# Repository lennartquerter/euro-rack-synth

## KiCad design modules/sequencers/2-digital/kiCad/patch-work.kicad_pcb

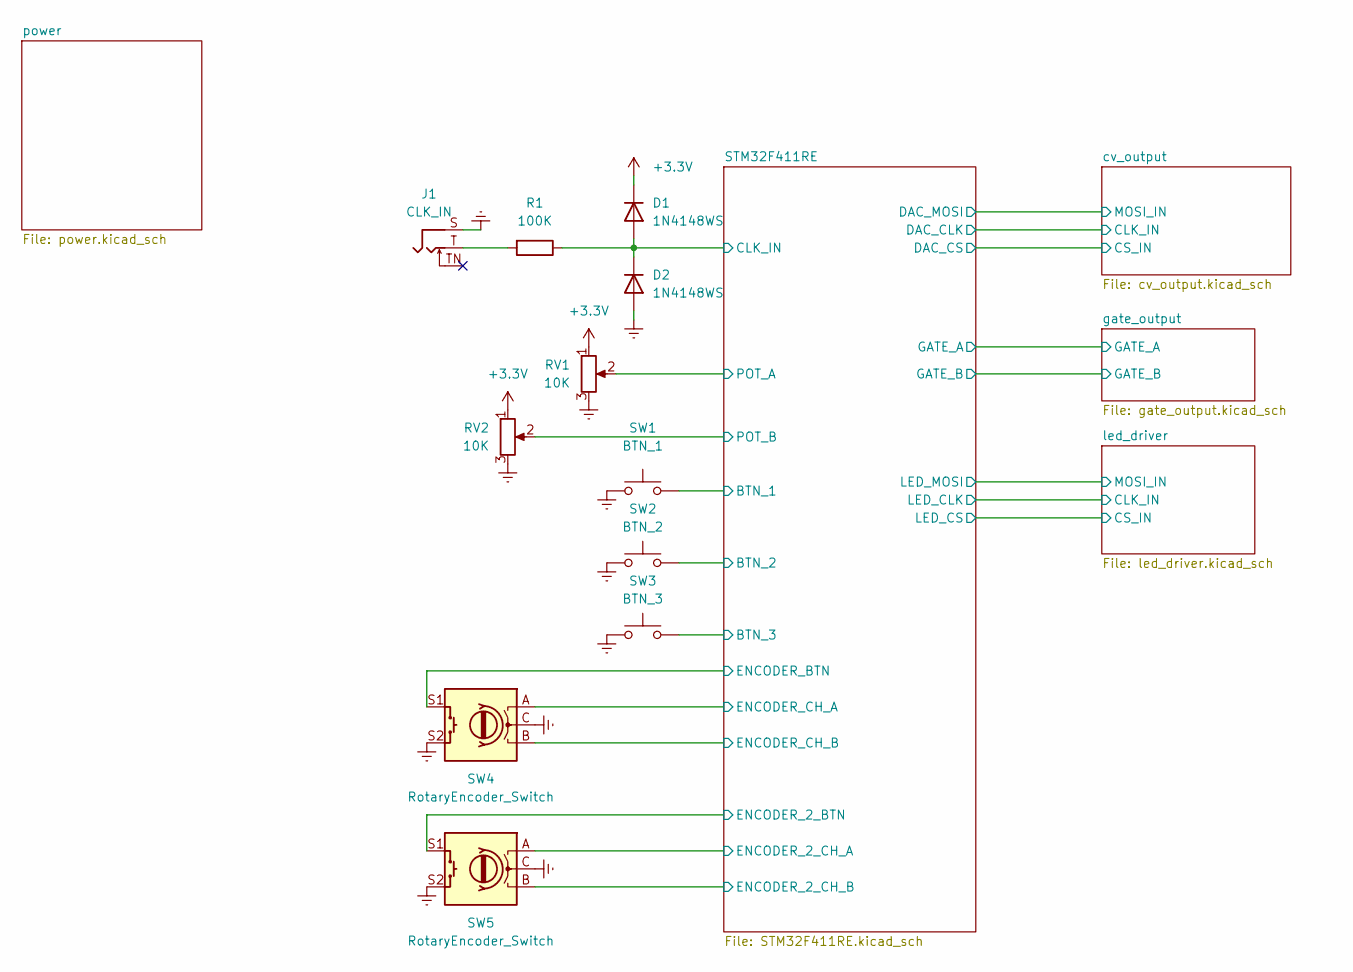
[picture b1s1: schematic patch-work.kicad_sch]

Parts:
D1, D2: 1N4148WS; D_SOD-323_HandSoldering
J1: CLK_IN; Jack_3.5mm_QingPu_WQP-PJ398SM_Vertical_CircularHoles
R1: 100K; R_0805_2012Metric_Pad1.20x1.40mm_HandSolder
RV1, RV2: 10K; Potentiometer_TT_P0915N
SW1: BTN_1; SW_PUSH_6mm
SW2: BTN_2; SW_PUSH_6mm
SW3: BTN_3; SW_PUSH_6mm
SW4, SW5: RotaryEncoder_Switch; RotaryEncoder_Alps_EC11E-Switch_Vertical_H20mm_CircularMoun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

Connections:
+3.3V: D1.1 (K), RV1.1, RV2.1; also elsewhere on the board
/STM32F411RE/BTN_1: SW1.2; also elsewhere on the board
/STM32F411RE/BTN_2: SW2.2; also elsewhere on the board
/STM32F411RE/BTN_3: SW3.2; also elsewhere on the board
/STM32F411RE/CLK_IN: D1.2 (A), D2.1 (K), R1.1; also elsewhere on the board
/STM32F411RE/ENCORDER_BTN: SW4.S1; also elsewhere on the board
/STM32F411RE/ENCORDER_TIM_C1: SW4.B; also elsewhere on the board
/STM32F411RE/ENCORDER_TIM_C2: SW4.A; also elsewhere on the board
/STM32F411RE/POT_A_ADC: RV1.2; also elsewhere on the board
/STM32F411RE/POT_B_ADC: RV2.2; also elsewhere on the board
/STM32F411RE/TIM4_BTN: SW5.S1; also elsewhere on the board
/STM32F411RE/TIM4_CH1: SW5.A; also elsewhere on the board
/STM32F411RE/TIM4_CH2: SW5.B; also elsewhere on the board
GNDREF: D2.2 (A), J1.S, RV1.3, RV2.3, SW1.1, SW2.1, SW3.1, SW4.C, SW4.S2, SW5.C, SW5.S2; also elsewhere on the board
unnamed: J1.T, R1.2

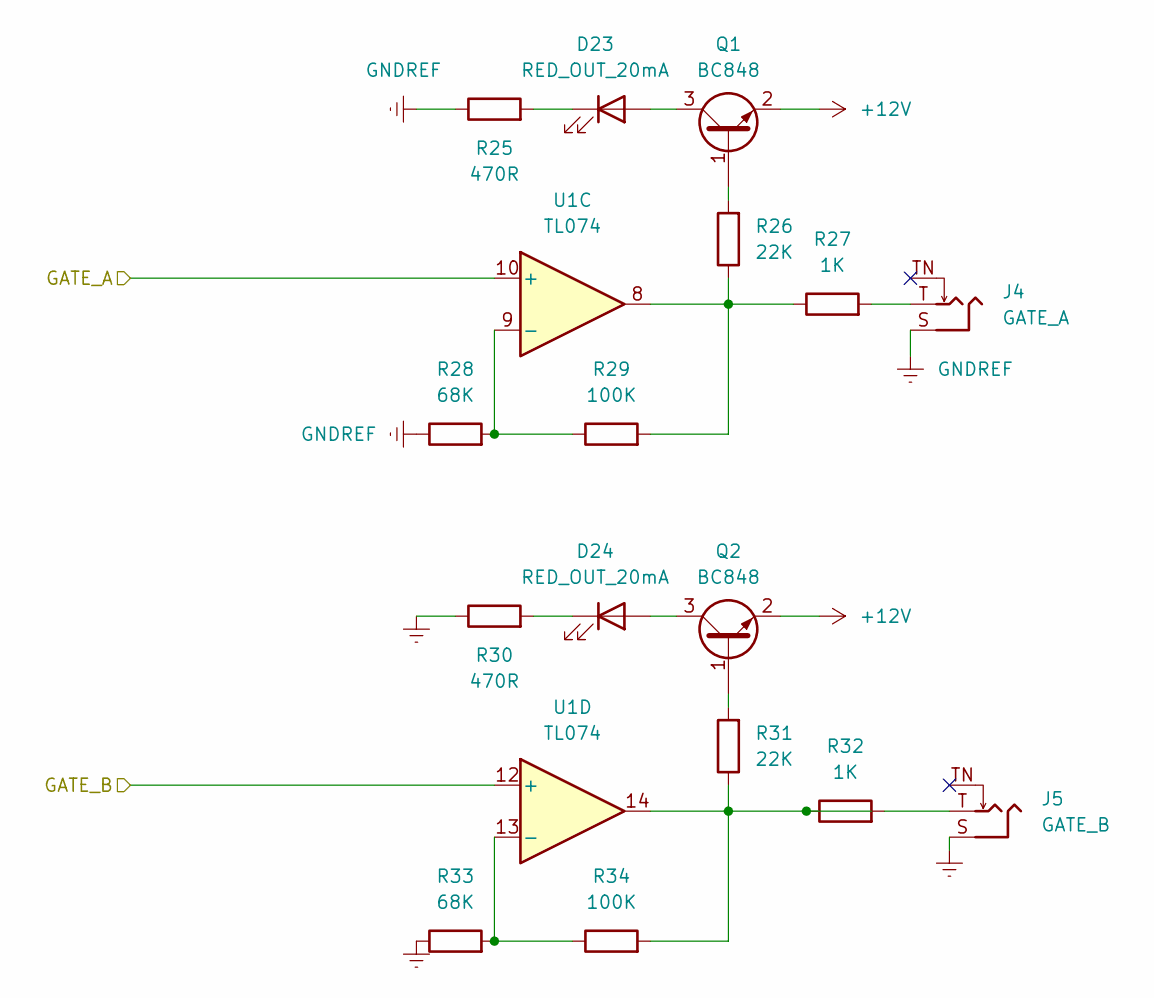
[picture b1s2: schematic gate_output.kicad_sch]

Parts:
D23, D24: RED_OUT_20mA; LED_D3.0mm
J4: GATE_A; Jack_3.5mm_QingPu_WQP-PJ398SM_Vertical_CircularHoles
J5: GATE_B; Jack_3.5mm_QingPu_WQP-PJ398SM_Vertical_CircularHoles
Q1, Q2: BC848; SOT-23
R25, R30: 470R; R_0805_2012Metric_Pad1.20x1.40mm_HandSolder
R26, R31: 22K; R_0805_2012Metric_Pad1.20x1.40mm_HandSolder
R27, R32: 1K; R_0805_2012Metric_Pad1.20x1.40mm_HandSolder
R28, R33: 68K; R_0805_2012Metric_Pad1.20x1.40mm_HandSolder
R29, R34: 100K; R_0805_2012Metric_Pad1.20x1.40mm_HandSolder
U1: TL074; SOIC-14

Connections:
+12V: Q1.2 (E), Q2.2 (E); also elsewhere on the board
/STM32F411RE/GATE_A_OUT: U1.10 (+); also elsewhere on the board
/STM32F411RE/GATE_B_OUT: U1.12 (+); also elsewhere on the board
GNDREF: J4.S, J5.S, R25.1, R28.1, R30.1, R33.1; also elsewhere on the board
unnamed: D23.2 (A), Q1.3 (C)
unnamed: D23.1 (K), R25.2
unnamed: D24.2 (A), Q2.3 (C)
unnamed: D24.1 (K), R30.2
unnamed: J4.T, R27.2
unnamed: J5.T, R32.2
unnamed: Q1.1 (B), R26.2
unnamed: Q2.1 (B), R31.2
unnamed: R26.1, R27.1, R29.2, U1.8
unnamed: R31.1, R32.1, R34.2, U1.14
unnamed: R28.2, R29.1, U1.9 (-)
unnamed: R33.2, R34.1, U1.13 (-)

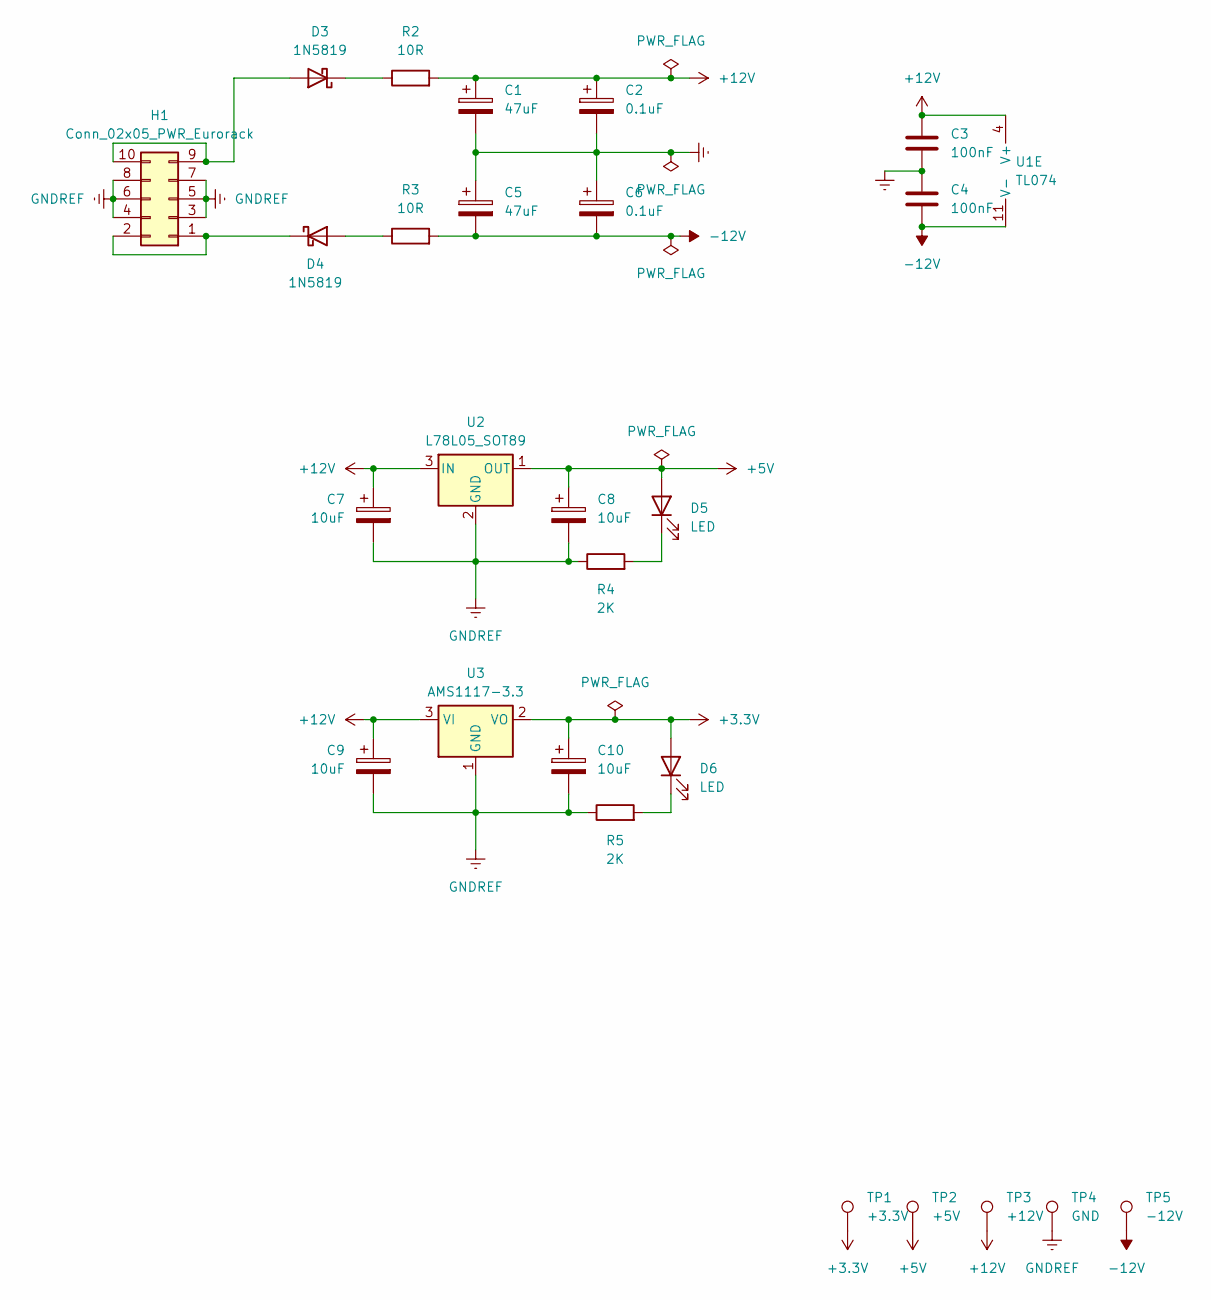
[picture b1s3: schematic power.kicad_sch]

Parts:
C1, C5: 47uF; CP_Radial_D6.3mm_P2.50mm
C2, C6: 0.1uF; CP_Radial_D4.0mm_P2.00mm
C3, C4: 100nF; C_0805_2012Metric_Pad1.18x1.45mm_HandSolder
C7, C8, C9, C10: 10uF; CP_Radial_D4.0mm_P2.00mm
D3, D4: 1N5819; D_SOD-123
D5, D6: LED; LED_0805_2012Metric_Pad1.15x1.40mm_HandSolder
H1: Conn_02x05_PWR_Eurorack; IDC-Header_2x05_P2.54mm_Vertical
R2, R3: 10R; R_0805_2012Metric_Pad1.20x1.40mm_HandSolder
R4, R5: 2K; R_0805_2012Metric_Pad1.20x1.40mm_HandSolder
TP1: +3.3V; Pin_D1.0mm_L10.0mm
TP2: +5V; Pin_D1.0mm_L10.0mm
TP3: +12V; Pin_D1.0mm_L10.0mm
TP4: GND; Pin_D1.0mm_L10.0mm
TP5: -12V; Pin_D1.0mm_L10.0mm
U1: TL074; SOIC-14
U2: L78L05_SOT89; SOT-89-3_Handsoldering
U3: AMS1117-3.3; SOT-223-3_TabPin2

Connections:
+3.3V: C10.1, D6.2 (A), TP1.1, U3.2 (VO); also elsewhere on the board
+5V: C8.1, D5.2 (A), TP2.1, U2.1 (OUT); also elsewhere on the board
+12V: C1.1, C2.1, C3.1, C7.1, C9.1, R2.2, TP3.1, U1.4 (V+), U2.3 (IN), U3.3 (VI); also elsewhere on the board
-12V: C4.2, C5.2, C6.2, R3.2, TP5.1, U1.11 (V-)
GNDREF: C1.2, C2.2, C3.2, C4.1, C5.1, C6.1, C7.2, C8.2, C9.2, C10.2, H1.3, H1.4, H1.5, H1.6, H1.7, H1.8, R4.1, R5.1, TP4.1, U2.2 (GND), U3.1 (GND); also elsewhere on the board
unnamed: D3.2 (A), H1.9, H1.10
unnamed: D3.1 (K), R2.1
unnamed: D4.2 (A), R3.1
unnamed: D4.1 (K), H1.1, H1.2
unnamed: D5.1 (K), R4.2
unnamed: D6.1 (K), R5.2

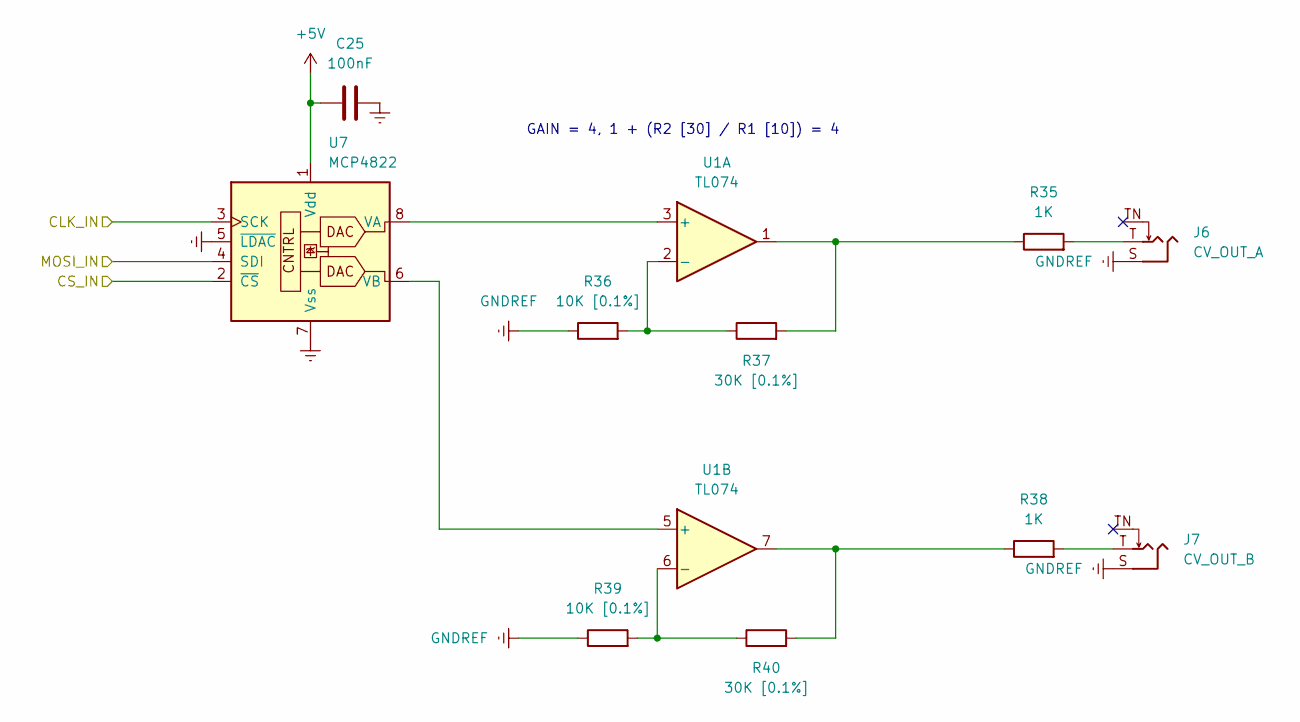
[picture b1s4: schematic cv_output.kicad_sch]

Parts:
C25: 100nF; C_0805_2012Metric_Pad1.18x1.45mm_HandSolder
J6: CV_OUT_A; Jack_3.5mm_QingPu_WQP-PJ398SM_Vertical_CircularHoles
J7: CV_OUT_B; Jack_3.5mm_QingPu_WQP-PJ398SM_Vertical_CircularHoles
R35, R38: 1K; R_0805_2012Metric_Pad1.20x1.40mm_HandSolder
R36, R39: 10K [0.1%]; R_0805_2012Metric_Pad1.20x1.40mm_HandSolder
R37, R40: 30K [0.1%]; R_0805_2012Metric_Pad1.20x1.40mm_HandSolder
U1: TL074; SOIC-14
U7: MCP4822; SOIC-8

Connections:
+5V: C25.1, U7.1 (Vdd); also elsewhere on the board
/STM32F411RE/SPI1_DAC_CLK: U7.3 (SCK); also elsewhere on the board
/STM32F411RE/SPI1_DAC_CV: U7.2 (~CS); also elsewhere on the board
/STM32F411RE/SPI1_DAC_MOSI: U7.4 (SDI); also elsewhere on the board
GNDREF: C25.2, J6.S, J7.S, R36.1, R39.1, U7.5 (~LDAC), U7.7 (Vss); also elsewhere on the board
unnamed: J6.T, R35.2
unnamed: J7.T, R38.2
unnamed: R35.1, R37.2, U1.1
unnamed: R38.1, R40.2, U1.7
unnamed: U1.3 (+), U7.8 (VA)
unnamed: R36.2, R37.1, U1.2 (-)
unnamed: U1.5 (+), U7.6 (VB)
unnamed: R39.2, R40.1, U1.6 (-)

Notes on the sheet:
GAIN = 4, 1 + (R2 [30] / R1 [10]) = 4

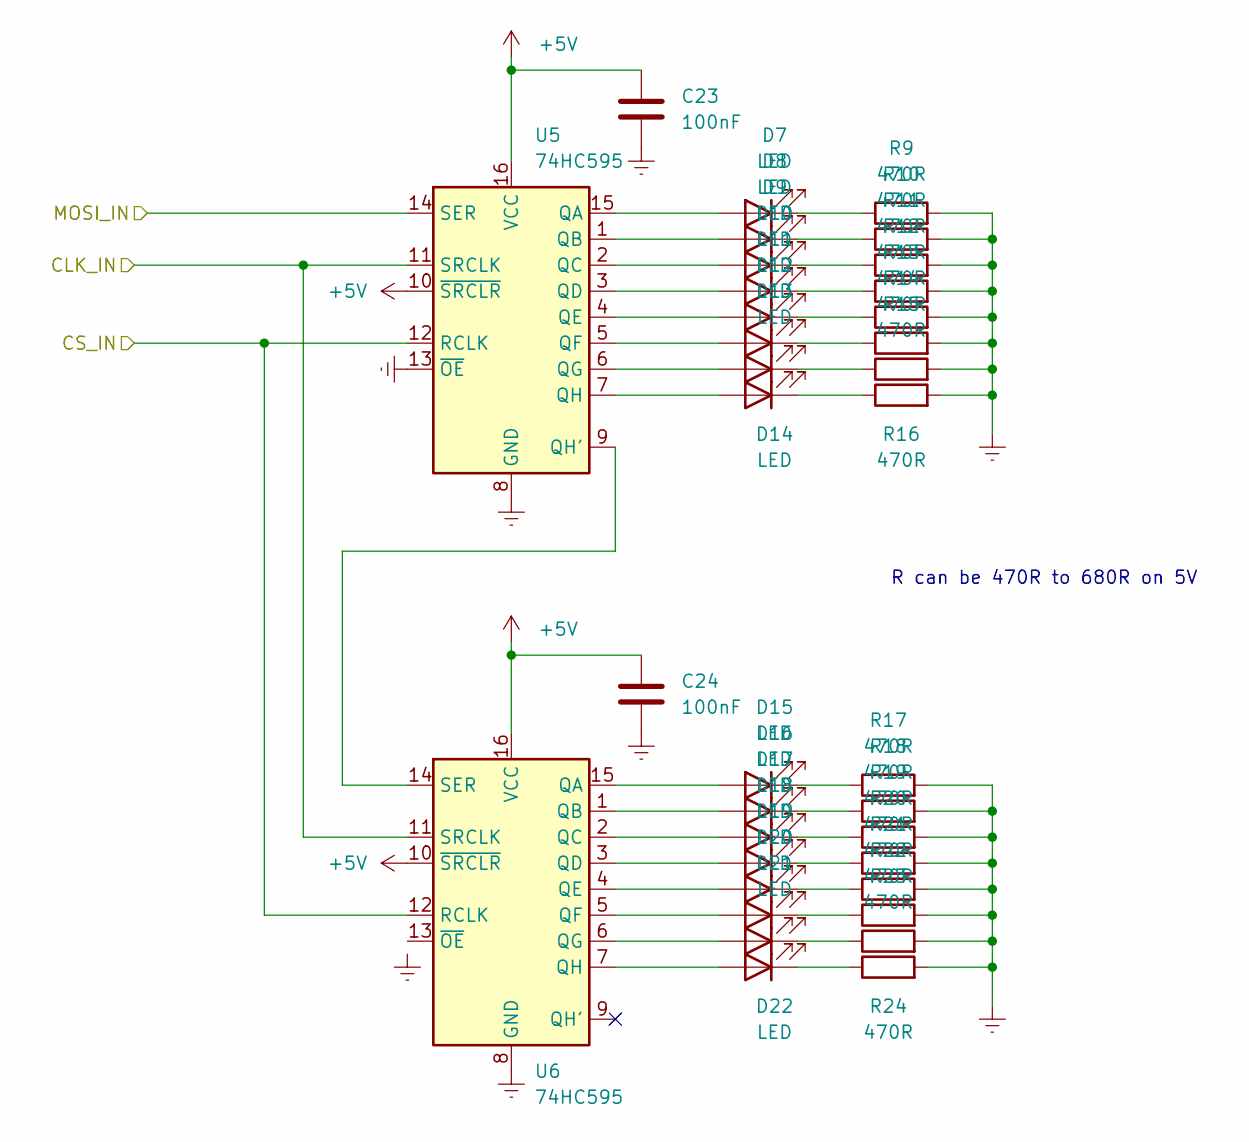
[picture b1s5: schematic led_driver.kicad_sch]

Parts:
C23, C24: 100nF; C_0805_2012Metric_Pad1.18x1.45mm_HandSolder
D7, D8, D9, D10, D11, D12, D13, D14, D15, D16, D17, D18, D19, D20, D21, D22: LED; LED_0805_2012Metric_Pad1.15x1.40mm_HandSolder
R9, R10, R11, R12, R13, R14, R15, R16, R17, R18, R19, R20, R21, R22, R23, R24: 470R; R_0805_2012Metric_Pad1.20x1.40mm_HandSolder
U5, U6: 74HC595; SOIC-16

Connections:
+5V: C23.2, C24.2, U5.10 (~SRCLR), U5.16 (VCC), U6.10 (~SRCLR), U6.16 (VCC); also elsewhere on the board
/STM32F411RE/SPI4_LED_CLK: U5.11 (SRCLK), U6.11 (SRCLK); also elsewhere on the board
/STM32F411RE/SPI4_LED_CS: U5.12 (RCLK), U6.12 (RCLK); also elsewhere on the board
/STM32F411RE/SPI4_LED_MOSI: U5.14 (SER); also elsewhere on the board
GNDREF: C23.1, C24.1, R9.2, R10.2, R11.2, R12.2, R13.2, R14.2, R15.2, R16.2, R17.2, R18.2, R19.2, R20.2, R21.2, R22.2, R23.2, R24.2, U5.8 (GND), U5.13 (~OE), U6.8 (GND); also elsewhere on the board
unnamed: D7.2 (A), U5.15 (QA)
unnamed: D7.1 (K), R9.1
unnamed: D8.2 (A), U5.1 (QB)
unnamed: D8.1 (K), R10.1
unnamed: D9.2 (A), U5.2 (QC)
unnamed: D9.1 (K), R11.1
unnamed: D10.2 (A), U5.3 (QD)
unnamed: D10.1 (K), R12.1
unnamed: D11.2 (A), U5.4 (QE)
unnamed: D11.1 (K), R13.1
unnamed: D12.2 (A), U5.5 (QF)
unnamed: D12.1 (K), R14.1
unnamed: D13.2 (A), U5.6 (QG)
unnamed: D13.1 (K), R15.1
unnamed: D14.2 (A), U5.7 (QH)
unnamed: D14.1 (K), R16.1
unnamed: D15.2 (A), U6.15 (QA)
unnamed: D15.1 (K), R17.1
unnamed: D16.2 (A), U6.1 (QB)
unnamed: D16.1 (K), R18.1
unnamed: D17.2 (A), U6.2 (QC)
unnamed: D17.1 (K), R19.1
unnamed: D18.2 (A), U6.3 (QD)
unnamed: D18.1 (K), R20.1
unnamed: D19.2 (A), U6.4 (QE)
unnamed: D19.1 (K), R21.1
unnamed: D20.2 (A), U6.5 (QF)
unnamed: D20.1 (K), R22.1
unnamed: D21.2 (A), U6.6 (QG)
unnamed: D21.1 (K), R23.1
unnamed: D22.2 (A), U6.7 (QH)
unnamed: D22.1 (K), R24.1
unnamed: U5.9 (QH'), U6.14 (SER)

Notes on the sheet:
R can be 470R to 680R on 5V

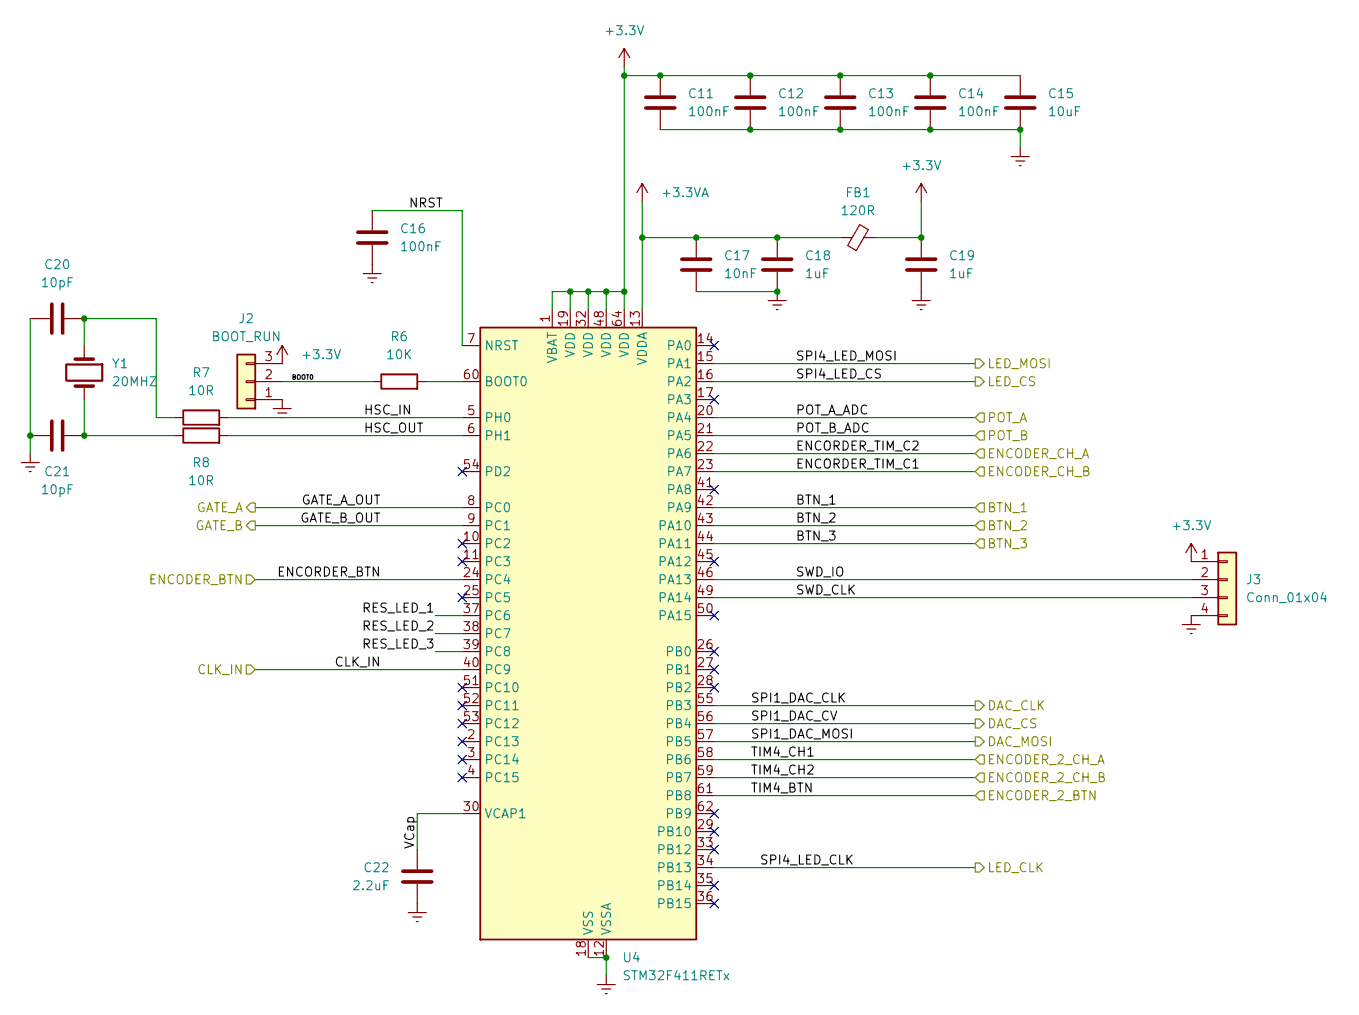
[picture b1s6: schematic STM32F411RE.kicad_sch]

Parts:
C11, C12, C13, C14, C16: 100nF; C_0805_2012Metric_Pad1.18x1.45mm_HandSolder
C15: 10uF; C_0805_2012Metric_Pad1.18x1.45mm_HandSolder
C17: 10nF; C_0805_2012Metric_Pad1.18x1.45mm_HandSolder
C18, C19: 1uF; C_0805_2012Metric_Pad1.18x1.45mm_HandSolder
C20, C21: 10pF; C_0805_2012Metric_Pad1.18x1.45mm_HandSolder
C22: 2.2uF; C_0805_2012Metric_Pad1.18x1.45mm_HandSolder
FB1: 120R; L_0805_2012Metric_Pad1.05x1.20mm_HandSolder
J2: BOOT_RUN; PinHeader_1x03_P2.54mm_Vertical
J3: Conn_01x04; PinHeader_1x04_P2.54mm_Vertical
R6: 10K; R_0805_2012Metric_Pad1.20x1.40mm_HandSolder
R7, R8: 10R; R_0805_2012Metric_Pad1.20x1.40mm_HandSolder
U4: STM32F411RETx; LQFP-64_10x10mm_P0.5mm
Y1: 20MHZ; Crystal_SMD_HC49-SD_HandSoldering

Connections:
+3.3V: C11.2, C12.2, C13.2, C14.2, C15.2, C19.2, FB1.2, J2.3, J3.1, U4.1 (VBAT), U4.19 (VDD), U4.32 (VDD), U4.48 (VDD), U4.64 (VDD); also elsewhere on the board
+3.3VA: C17.2, C18.2, FB1.1, U4.13 (VDDA)
/STM32F411RE/BOOT0: J2.2, R6.1
/STM32F411RE/BTN_1: U4.42 (PA9); also elsewhere on the board
/STM32F411RE/BTN_2: U4.43 (PA10); also elsewhere on the board
/STM32F411RE/BTN_3: U4.44 (PA11); also elsewhere on the board
/STM32F411RE/CLK_IN: U4.40 (PC9); also elsewhere on the board
/STM32F411RE/ENCORDER_BTN: U4.24 (PC4); also elsewhere on the board
/STM32F411RE/ENCORDER_TIM_C1: U4.23 (PA7); also elsewhere on the board
/STM32F411RE/ENCORDER_TIM_C2: U4.22 (PA6); also elsewhere on the board
/STM32F411RE/GATE_A_OUT: U4.8 (PC0); also elsewhere on the board
/STM32F411RE/GATE_B_OUT: U4.9 (PC1); also elsewhere on the board
/STM32F411RE/HSC_IN: R7.2, U4.5 (PH0)
/STM32F411RE/HSC_OUT: R8.2, U4.6 (PH1)
/STM32F411RE/NRST: C16.1, U4.7 (NRST)
/STM32F411RE/POT_A_ADC: U4.20 (PA4); also elsewhere on the board
/STM32F411RE/POT_B_ADC: U4.21 (PA5); also elsewhere on the board
/STM32F411RE/RES_LED_1: U4.37 (PC6)
/STM32F411RE/RES_LED_2: U4.38 (PC7)
/STM32F411RE/RES_LED_3: U4.39 (PC8)
/STM32F411RE/SPI1_DAC_CLK: U4.55 (PB3); also elsewhere on the board
/STM32F411RE/SPI1_DAC_CV: U4.56 (PB4); also elsewhere on the board
/STM32F411RE/SPI1_DAC_MOSI: U4.57 (PB5); also elsewhere on the board
/STM32F411RE/SPI4_LED_CLK: U4.34 (PB13); also elsewhere on the board
/STM32F411RE/SPI4_LED_CS: U4.16 (PA2); also elsewhere on the board
/STM32F411RE/SPI4_LED_MOSI: U4.15 (PA1); also elsewhere on the board
/STM32F411RE/SWD_CLK: J3.3, U4.49 (PA14)
/STM32F411RE/SWD_IO: J3.2, U4.46 (PA13)
/STM32F411RE/TIM4_BTN: U4.61 (PB8); also elsewhere on the board
/STM32F411RE/TIM4_CH1: U4.58 (PB6); also elsewhere on the board
/STM32F411RE/TIM4_CH2: U4.59 (PB7); also elsewhere on the board
/STM32F411RE/VCap: C22.1, U4.30 (VCAP1)
GNDREF: C11.1, C12.1, C13.1, C14.1, C15.1, C16.2, C17.1, C18.1, C19.1, C20.2, C21.2, C22.2, J2.1, J3.4, U4.12 (VSSA), U4.18 (VSS), U4.31 (VSS), U4.47 (VSS), U4.63 (VSS); also elsewhere on the board
unnamed: C20.1, R7.1, Y1.1
unnamed: C21.1, R8.1, Y1.2
unnamed: R6.2, U4.60 (BOOT0)

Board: 2 copper layers, 120 parts (74 on the bottom side), 96 nets, no tracks yet.

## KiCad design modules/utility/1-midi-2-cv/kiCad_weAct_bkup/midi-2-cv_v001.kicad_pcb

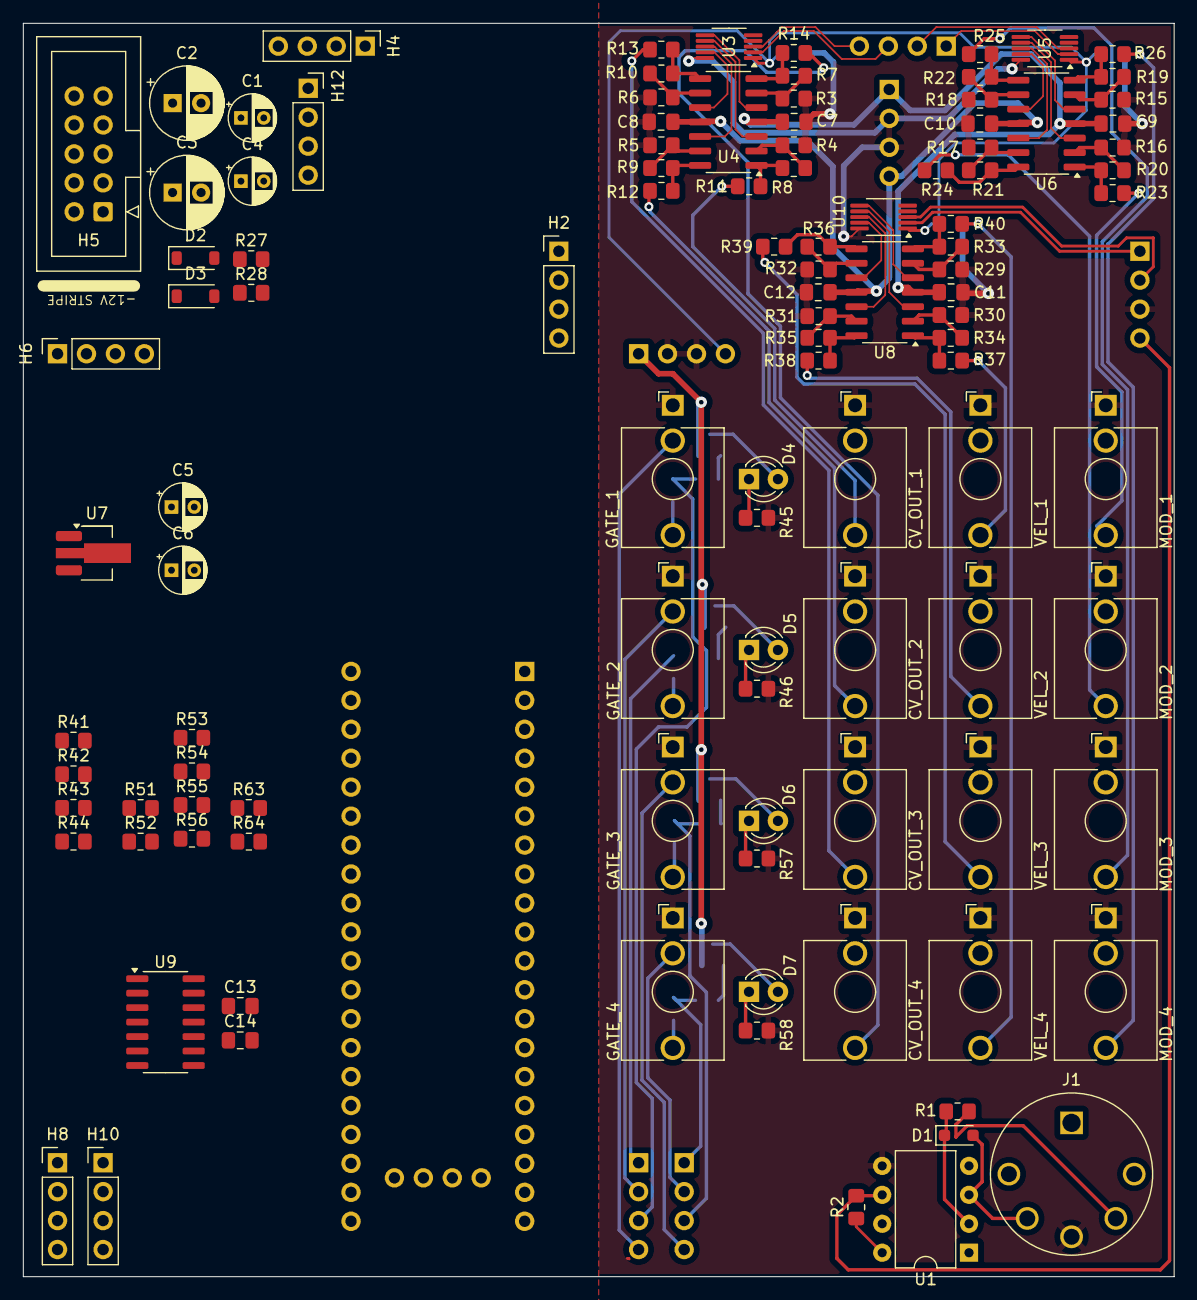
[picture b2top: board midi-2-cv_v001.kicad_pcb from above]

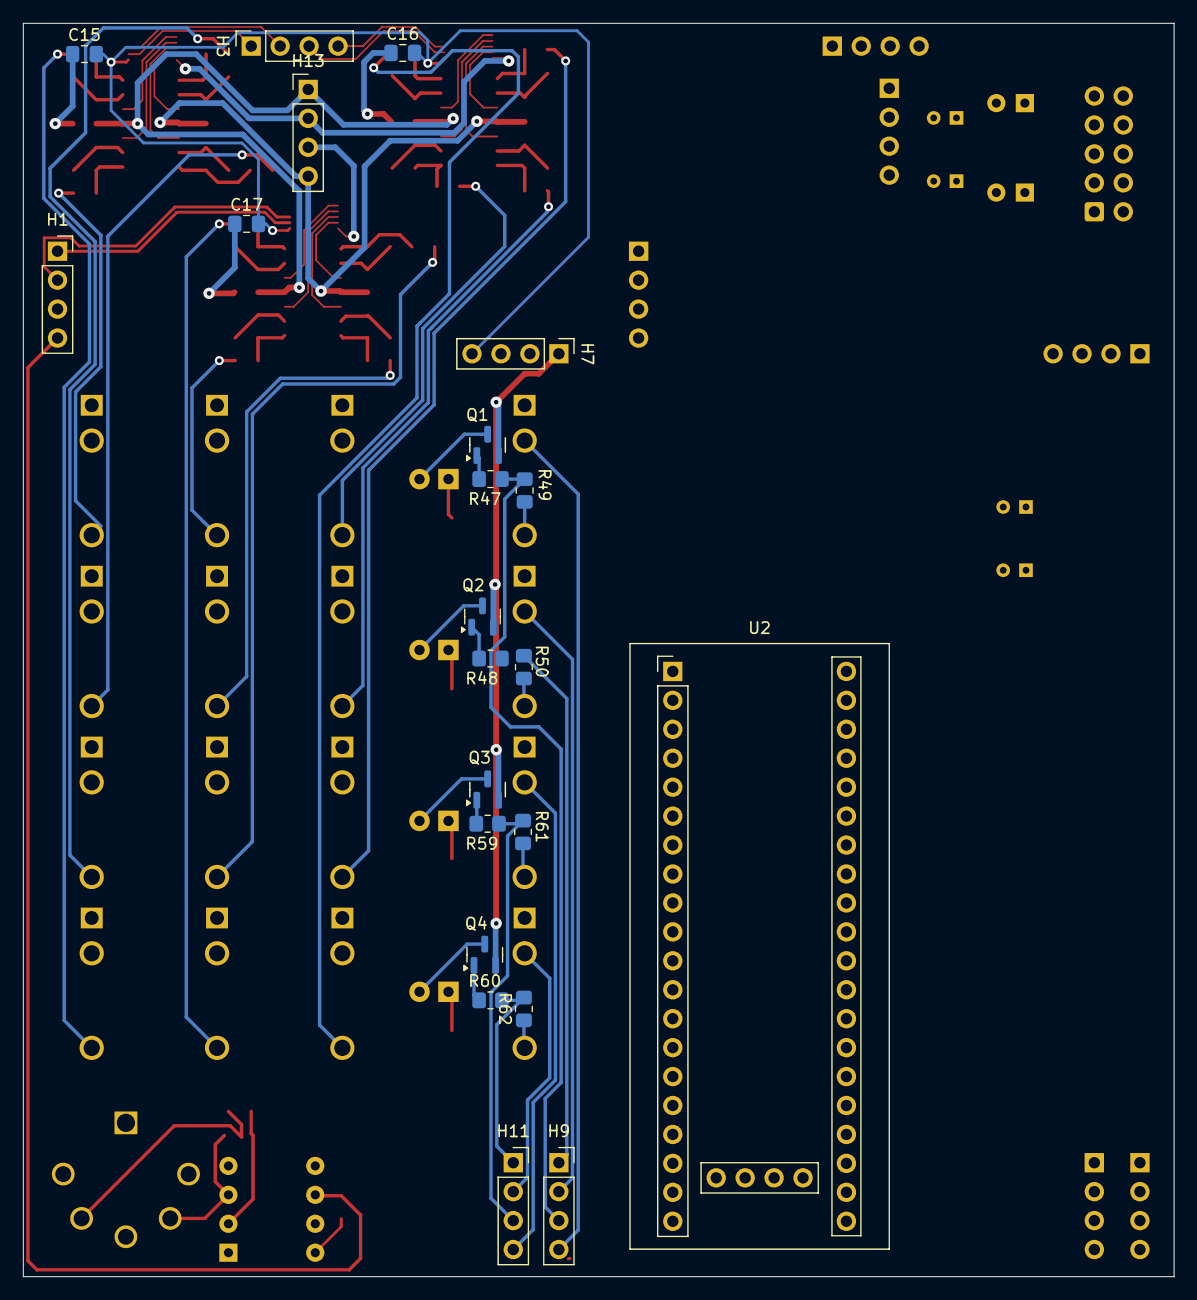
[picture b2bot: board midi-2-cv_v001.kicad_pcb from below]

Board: 2 copper layers, 101.0 x 110.0 mm, 132 parts (22 on the bottom side), 114 nets.

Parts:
C1, C4, C5, C6: 0.1uF; CP_Radial_D4.0mm_P2.00mm
C2, C3: 47uF; CP_Radial_D6.3mm_P2.50mm
C7, C8, C9, C10, C11, C12, C13, C14, C15, C16, C17: 0.1uF; C_0805_2012Metric_Pad1.18x1.45mm_HandSolder
CV_OUT_1: CV_OUT_2; Jack_3.5mm_QingPu_WQP-PJ398SM_Vertical_CircularHoles
CV_OUT_2: CV_OUT_3; Jack_3.5mm_QingPu_WQP-PJ398SM_Vertical_CircularHoles
CV_OUT_3: CV_OUT_4; Jack_3.5mm_QingPu_WQP-PJ398SM_Vertical_CircularHoles
CV_OUT_4: CV_OUT_1; Jack_3.5mm_QingPu_WQP-PJ398SM_Vertical_CircularHoles
D1: 1N4148; D_SOD-323_HandSoldering
D2, D3: 1N5819; D_SOD-123
D4, D5, D6, D7: RED_OUT_20mA; LED_D3.0mm
GATE_1: GATE_2; Jack_3.5mm_QingPu_WQP-PJ398SM_Vertical_CircularHoles
GATE_2: GATE_1; Jack_3.5mm_QingPu_WQP-PJ398SM_Vertical_CircularHoles
GATE_3: GATE_3; Jack_3.5mm_QingPu_WQP-PJ398SM_Vertical_CircularHoles
GATE_4: GATE_4; Jack_3.5mm_QingPu_WQP-PJ398SM_Vertical_CircularHoles
H1, H3, H6, H9, H11, H12: PinSocket_01x04; PinSocket_1x04_P2.54mm_Vertical
H2, H4, H7, H8, H10, H13: PinHeader_01x04; PinHeader_1x04_P2.54mm_Vertical
H5: Conn_02x05_PWR_Eurorack; IDC-Header_2x05_P2.54mm_Vertical
J1: DIN-6; MIDI_DIN5-SD-60BV
MOD_1: MOD_2; Jack_3.5mm_QingPu_WQP-PJ398SM_Vertical_CircularHoles
MOD_2: MOD_3; Jack_3.5mm_QingPu_WQP-PJ398SM_Vertical_CircularHoles
MOD_3: MOD_4; Jack_3.5mm_QingPu_WQP-PJ398SM_Vertical_CircularHoles
MOD_4: MOD_1; Jack_3.5mm_QingPu_WQP-PJ398SM_Vertical_CircularHoles
Q1, Q2, Q3, Q4: BC848; SOT-23
R1: 220R; R_0805_2012Metric_Pad1.20x1.40mm_HandSolder
R2: 10K; R_0805_2012Metric_Pad1.20x1.40mm_HandSolder
R3, R4, R5, R6, R15, R16, R17, R18, R29, R30, R31, R32: 10K [1%]; R_0805_2012Metric_Pad1.20x1.40mm_HandSolder
R7, R8, R9, R10, R19, R20, R21, R22, R33, R34, R35, R36: 47K [1%]; R_0805_2012Metric_Pad1.20x1.40mm_HandSolder
R11, R12, R13, R14, R23, R24, R25, R26, R37, R38, R39, R40, R49, R50, R61, R62: 1K; R_0805_2012Metric_Pad1.20x1.40mm_HandSolder
R27, R28: 10; R_0805_2012Metric_Pad1.20x1.40mm_HandSolder
R41, R42, R53, R54: 68K; R_0805_2012Metric_Pad1.20x1.40mm_HandSolder
R43, R44, R51, R52, R55, R56, R63, R64: 100K; R_0805_2012Metric_Pad1.20x1.40mm_HandSolder
R45, R46, R57, R58: 470R; R_0805_2012Metric_Pad1.20x1.40mm_HandSolder
R47, R48, R59, R60: 22K; R_0805_2012Metric_Pad1.20x1.40mm_HandSolder
U1: 6N135; DIP-8_W7.62mm
U2: YAAJ_WeAct_BlackPill_Part_Like; YAAJ_WeAct_BlackPill_SWD_2
U3, U5, U10: MCP4728; MSOP-10_3x3mm_P0.5mm
U4, U6, U8, U9: TL074; SOIC-14_3.9x8.7mm_P1.27mm
U7: L7805; SOT-89-3_Handsoldering
VEL_1: VEL_2; Jack_3.5mm_QingPu_WQP-PJ398SM_Vertical_CircularHoles
VEL_2: VEL_3; Jack_3.5mm_QingPu_WQP-PJ398SM_Vertical_CircularHoles
VEL_3: VEL_4; Jack_3.5mm_QingPu_WQP-PJ398SM_Vertical_CircularHoles
VEL_4: VEL_1; Jack_3.5mm_QingPu_WQP-PJ398SM_Vertical_CircularHoles

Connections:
+3.3V: R2.1, R51.1, R52.1, R63.1, R64.1, U1.8, U2.20 (3V3), U2.38 (3V3)
+5V: C4.1, C15.2, C16.2, C17.2, H6.4, H7.4, U2.18 (5V), U2.40 (5V), U3.1 (VDD), U5.1 (VDD), U7.3 (OUT), U10.1 (VDD)
+12V: C1.1, C2.1, C5.1, C7.1, C9.1, C11.1, C13.1, H6.1, H7.1, H12.1, H13.1, Q1.2 (E), Q2.2 (E), Q3.2 (E), Q4.2 (E), R27.1, U4.4 (V+), U6.4 (V+), U7.1 (IN), U8.4 (V+), U9.4 (V+)
-12V: C3.2, C6.2, C8.2, C10.2, C12.2, C14.2, H12.4, H13.4, R28.1, U4.11 (V-), U6.11 (V-), U8.11 (V-), U9.11 (V-)
/gate_out/GATE_1_CALLBACK: H8.2, R52.2, U2.26 (PA0)
/gate_out/GATE_2_CALLBACK: H8.4, R51.2, U2.27 (PA1)
/gate_out/GATE_3_CALLBACK: H10.4, R63.2, U2.28 (PA2)
/gate_out/GATE_4_CALLBACK: H10.2, R64.2, U2.29 (PA3)
/gate_out/GATE_IN_1: U2.1 (PB12), U9.3 (+)
/gate_out/GATE_IN_2: U2.2 (PB13), U9.5 (+)
/gate_out/GATE_IN_3: U2.3 (PB14), U9.10 (+)
/gate_out/GATE_IN_4: U2.4 (PB15), U9.12 (+)
/mcp4728_cv-out/SCL: H3.3, U3.2 (SCL)
/mcp4728_cv-out/SDA: H3.4, U3.3 (SDA)
/mcp4728_mod-wheel-out/SCL: H1.1, U5.2 (SCL)
/mcp4728_mod-wheel-out/SDA: H1.2, U5.3 (SDA)
/mcp4728_velocity-out/SCL: H3.1, U10.2 (SCL)
/mcp4728_velocity-out/SDA: H3.2, U10.3 (SDA)
GNDREF: C1.2, C2.2, C3.1, C4.2, C5.2, C6.1, C7.2, C8.1, C9.2, C10.1, C11.2, C12.1, C13.2, C14.1, C15.1, C16.1, C17.1, CV_OUT_1.S, CV_OUT_2.S, CV_OUT_3.S, CV_OUT_4.S, GATE_1.S, GATE_2.S, GATE_3.S, GATE_4.S, H1.3, H2.3, H5.3, H5.4, H5.5, H5.6, H5.7, H5.8, H6.2, H6.3, H7.2, H7.3, H12.2, H12.3, H13.2, H13.3, J1.3, MOD_1.S, MOD_2.S, MOD_3.S, MOD_4.S, R3.2, R4.2, R5.2, R6.2, R15.2, R16.2, R17.2, R18.2, R29.2, R30.2, R31.2, R32.2, R41.2, R42.2, R45.2, R46.2, R53.2, R54.2, R57.2, R58.2, U1.5, U2.19 (GND), U2.39 (GND), U3.10 (VSS), U5.10 (VSS), U7.2 (GND), U10.10 (VSS), VEL_1.S, VEL_2.S, VEL_3.S, VEL_4.S
unnamed: CV_OUT_1.T, R11.1
unnamed: CV_OUT_2.T, R12.1
unnamed: CV_OUT_3.T, R13.1
unnamed: CV_OUT_4.T, R14.1
unnamed: D1.2 (A), J1.4, U1.3
unnamed: D1.1 (K), R1.2, U1.2
unnamed: D2.2 (A), H5.9, H5.10
unnamed: D2.1 (K), R27.2
unnamed: D3.2 (A), R28.2
unnamed: D3.1 (K), H5.1, H5.2
unnamed: D4.2 (A), Q1.3 (C)
unnamed: D4.1 (K), R45.1
unnamed: D5.2 (A), Q2.3 (C)
unnamed: D5.1 (K), R46.1
unnamed: D6.2 (A), Q3.3 (C)
unnamed: D6.1 (K), R57.1
unnamed: D7.2 (A), Q4.3 (C)
unnamed: D7.1 (K), R58.1
unnamed: GATE_1.T, R49.1
unnamed: GATE_2.T, R50.1
unnamed: GATE_3.T, R61.1
unnamed: GATE_4.T, R62.1
unnamed: H1.4, R2.2, U1.6
unnamed: H2.1, U2.16 (PB8)
unnamed: H2.2, U2.12 (PB4)
unnamed: H2.4, U2.7 (PA10)
unnamed: H4.1, U2.37 (PB10)
unnamed: H4.2, U2.11 (PB3)
unnamed: H4.3, U2.14 (PB6)
unnamed: H4.4, U2.15 (PB7)
unnamed: H8.1, R44.1, U9.1
unnamed: H8.3, R43.1, U9.7
unnamed: H9.1, R48.2, R50.2
unnamed: GATE_2.TN, H9.2
unnamed: H9.3, R47.2, R49.2
unnamed: GATE_1.TN, H9.4
unnamed: H10.1, R56.1, U9.14
unnamed: H10.3, R55.1, U9.8
unnamed: H11.1, R60.2, R62.2
unnamed: GATE_4.TN, H11.2
unnamed: H11.3, R59.2, R61.2
unnamed: GATE_3.TN, H11.4
unnamed: J1.2, R1.1
unnamed: MOD_1.T, R23.1
unnamed: MOD_2.T, R24.1
unnamed: MOD_3.T, R25.1
unnamed: MOD_4.T, R26.1
unnamed: Q1.1 (B), R47.1
unnamed: Q2.1 (B), R48.1
unnamed: Q3.1 (B), R59.1
unnamed: Q4.1 (B), R60.1
unnamed: R10.1, R13.2, U4.8
unnamed: R8.1, R11.2, U4.1
unnamed: R9.1, R12.2, U4.14
unnamed: R7.1, R14.2, U4.7
unnamed: R19.1, R26.2, U6.7
unnamed: R20.1, R23.2, U6.1
unnamed: R21.1, R24.2, U6.14
unnamed: R22.1, R25.2, U6.8
unnamed: R33.1, R40.2, U8.7
unnamed: R34.1, R37.2, U8.1
unnamed: R35.1, R38.2, U8.14
unnamed: R36.1, R39.2, U8.8
unnamed: R37.1, VEL_1.T
unnamed: R38.1, VEL_2.T
unnamed: R39.1, VEL_3.T
unnamed: R40.1, VEL_4.T
unnamed: U3.6 (VOUTA), U4.5 (+)
unnamed: U3.7 (VOUTB), U4.3 (+)
unnamed: U3.8 (VOUTC), U4.12 (+)
unnamed: U3.9 (VOUTD), U4.10 (+)
unnamed: R4.1, R8.2, U4.2 (-)
unnamed: R3.1, R7.2, U4.6 (-)
unnamed: R6.1, R10.2, U4.9 (-)
unnamed: R5.1, R9.2, U4.13 (-)
unnamed: U5.6 (VOUTA), U6.5 (+)
unnamed: U5.7 (VOUTB), U6.3 (+)
unnamed: U5.8 (VOUTC), U6.12 (+)
unnamed: U5.9 (VOUTD), U6.10 (+)
unnamed: R16.1, R20.2, U6.2 (-)
unnamed: R15.1, R19.2, U6.6 (-)
unnamed: R18.1, R22.2, U6.9 (-)
unnamed: R17.1, R21.2, U6.13 (-)
unnamed: R30.1, R34.2, U8.2 (-)
unnamed: R29.1, R33.2, U8.6 (-)
unnamed: R32.1, R36.2, U8.9 (-)
unnamed: R31.1, R35.2, U8.13 (-)
unnamed: R42.1, R44.2, U9.2 (-)
unnamed: R41.1, R43.2, U9.6 (-)
unnamed: R54.1, R55.2, U9.9 (-)
unnamed: R53.1, R56.2, U9.13 (-)
unnamed: U8.5 (+), U10.6 (VOUTA)
unnamed: U8.3 (+), U10.7 (VOUTB)
unnamed: U8.12 (+), U10.8 (VOUTC)
unnamed: U8.10 (+), U10.9 (VOUTD)
